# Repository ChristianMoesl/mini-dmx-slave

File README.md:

# Mini DMX-Slave
A small LED controller, to power a RGBW LED Spot between 8-24V through PWM.

##  LICENSE
The contents of this repository are covered under the [MIT License](./LICENSE).

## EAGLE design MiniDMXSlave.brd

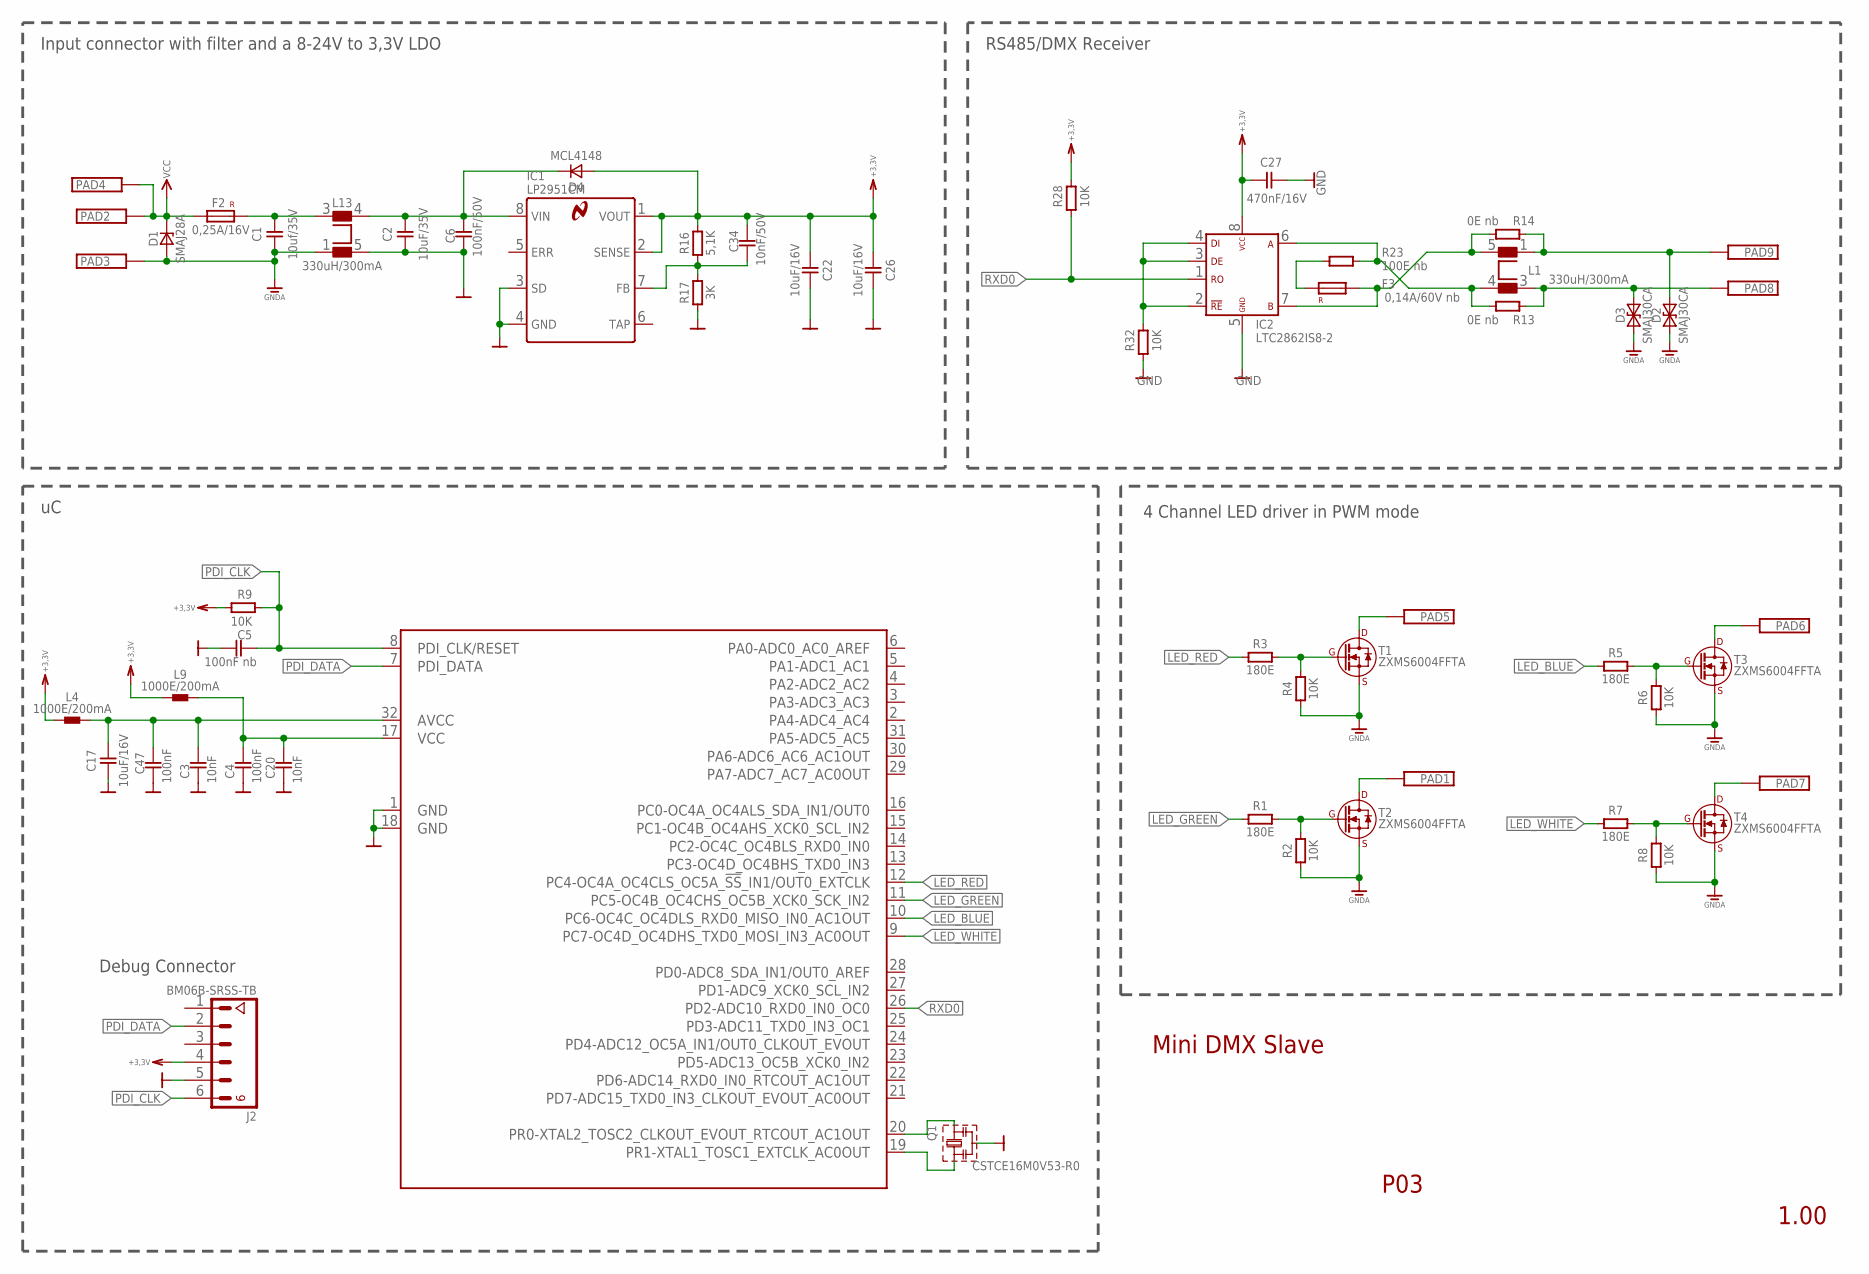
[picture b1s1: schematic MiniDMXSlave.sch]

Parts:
C1: 10uf/35V; 1206
C2: 10uF/35V; 1206
C3, C20: 10nF; 0603
C4, C47: 100nF; 0603
C5: 100nF nb; 0603
C6: 100nF/50V; 0603
C17, C22, C26: 10uF/16V; 0805
C27: 470nF/16V; 0603
C34: 10nF/50V; 0603
D1: SMAJ28A; DO-214AC
D2, D3: SMAJ30CA; DO-214AC
D4: MCL4148; MICROMELF
F2: 0,25A/16V; 1206L
F3: 0,14A/60V nb; 1812L
IC1: LP2951CM; SO8
IC2: LTC2862IS8-2; SO8
IC3: E5-TQFP; TQFP32
J2: BM06B-SRSS-TB
L1, L13: 330uH/300mA; WE-SL1
L4, L9: 1000E/200mA; 0603
PAD1, PAD2, PAD3, PAD4, PAD5, PAD6, PAD7, PAD8, PAD9: PADS-6X3; PAD_6MMX3MM
Q1: CSTCE16M0V53-R0; CSTCE_G_&_V
R1, R3, R5, R7: 180E; 0603
R2, R4, R6, R8, R9, R28, R32: 10K; 0603
R13, R14: 0E nb; 0805
R16: 5,1K; 0603
R17: 3K; 0603
R23: 100E nb; 0207
T1, T2, T3, T4: ZXMS6004FFTA; SOT-23

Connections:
+3,3V: C22.1, C26.1, C27.2, C34.2, D4.A, IC1.1 (VOUT), IC1.2 (SENSE), IC2.8 (VCC), J2.4, L4.1, L9.1, R9.2, R16.2, R28.2
DHGFHDFGJDJF: C3.2, C17.2, C47.2, IC3.32 (AVCC), L4.2
GND: C2.1, C3.1, C4.1, C5.2, C6.1, C17.1, C20.1, C22.2, C26.2, C27.1, C47.1, IC1.3 (SD), IC1.4 (GND), IC2.5 (GND), IC3.1 (GND), IC3.18 (GND), J2.5, L13.5 (2), Q1.2 (GND), R17.1, R32.1
GNDA: C1.1, D1.A, D2.K (2), D3.K (2), L13.1, PAD3.1, R2.1, R4.1, R6.1, R8.1, T1.2 (S), T2.2 (S), T3.2 (S), T4.2 (S)
LED_BLUE: IC3.10 (PC6-OC4C_OC4DLS_RXD0_MISO_IN0_AC1OUT), R5.1
LED_GREEN: IC3.11 (PC5-OC4B_OC4CHS_OC5B_XCK0_SCK_IN2), R1.1
LED_RED: IC3.12 (PC4-OC4A_OC4CLS_OC5A_!SS!_IN1/OUT0_EXTC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), R3.1
LED_WHITE: IC3.9 (PC7-OC4D_OC4DHS_TXD0_MOSI_IN3_AC0OUT), R7.1
unnamed: PAD1.1, T2.3 (D)
unnamed: R1.2, R2.2, T2.1 (G)
unnamed: R3.2, R4.2, T1.1 (G)
unnamed: C2.2, C6.2, D4.K, IC1.8 (VIN), L13.4 (3)
unnamed: PAD5.1, T1.3 (D)
unnamed: R5.2, R6.2, T3.1 (G)
unnamed: PAD6.1, T3.3 (D)
unnamed: R7.2, R8.2, T4.1 (G)
unnamed: C34.1, IC1.7 (FB), R16.1, R17.2
unnamed: PAD7.1, T4.3 (D)
unnamed: IC3.20 (PR0-XTAL2_TOSC2_CLKOUT_EVOUT_RTCOUT_AC1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), Q1.3 (OSC2)
unnamed: C1.2, F2.2, L13.3 (4)
unnamed: IC3.19 (PR1-XTAL1_TOSC1_EXTCLK_AC0OUT), Q1.1 (OSC1)
unnamed: F3.2, R23.1
PDI_CLK: C5.1, IC3.8 (PDI_CLK/RESET), J2.6, R9.1
PDI_DATA: IC3.7 (PDI_DATA), J2.2
QFASFG: C4.2, C20.2, IC3.17 (VCC), L9.2
RS485_A: D3.A (1), L1.3 (4), PAD8.1, R13.1
RS485_A1: IC2.6 (A), L1.4 (3), R13.2, R23.2
RS485_B: D2.A (1), L1.1, PAD9.1, R14.1
RS485_B0: F3.1, IC2.7 (B), L1.5 (2), R14.2
RXD0: IC2.1 (R0), IC3.26 (PD2-ADC10_RXD0_IN0_OC0), R28.1
TXD0_ENA: IC2.2 (/RE), IC2.3 (DE), IC2.4 (DI), R32.2
VCC: D1.K, F2.1, PAD2.1, PAD4.1

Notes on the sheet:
Debug Connector
Input connector with filter and a 8-24V to 3,3V LDO
RS485/DMX Receiver
4 Channel LED driver in PWM mode
Mini DMX Slave
P03
1.00

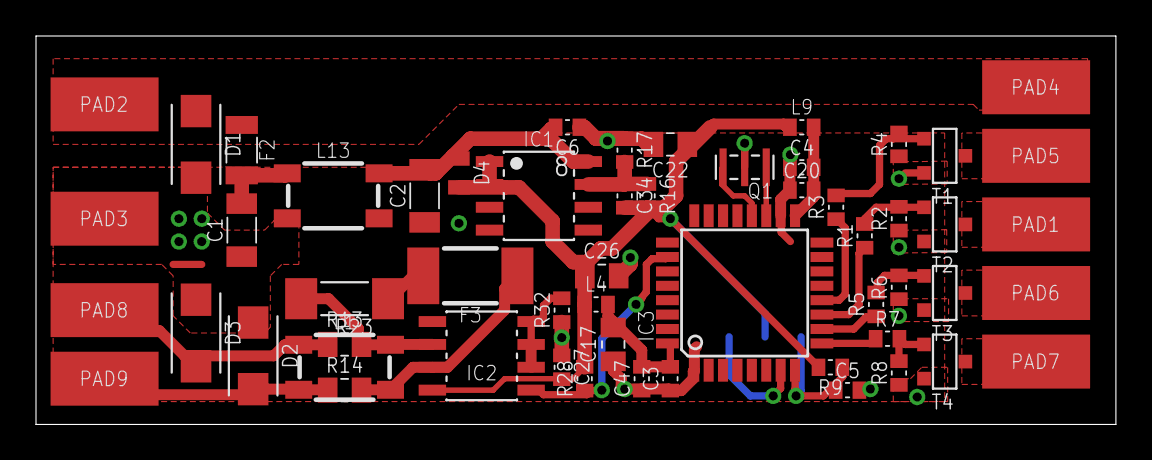
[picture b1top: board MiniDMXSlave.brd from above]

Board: 2 copper layers, 60.0 x 21.6 mm, 57 parts (1 on the bottom side), 32 nets.
